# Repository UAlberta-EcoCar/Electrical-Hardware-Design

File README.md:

View this project on [CADLAB.io](https://cadlab.io/project/29517). 

# Electrical-Design-Hardware

**Do not merge branches to main yet, this may be done in the future**

Contains the hardware design for the upcoming prototype vehicle.  Each Branch in this repo has its own board design and schematic files for each car.  Add the entire repo to a filepath ia GitHub Desktop by adding the link into the "Current Repository" panel or with the following via a console:

```
cd Documents\GitHub                                                            #Change your directory where desired
git clone https://github.com/UAlberta-EcoCar/Electrical-Hardware-Design        #Clone the repo
cd Documents\GitHub\Electrical-Hardware-Design                                 #Change your directory into the repo
git branch -r                                                                  #Displays all remote branches, choose the branch you're looking for 
git checkout Relay-Board                                                       #branch that is desired (I used Relay-Board as an example).  
```
After making changes the remote branch can be updated with the following:
```
git add .                                                                      #Adds your modified files to the quene to be committed later
git commit -m "your-commit-message"                                            #Commits the files to a new revision of the branch with a log
git push                                                                       #Pushes the changes to the remote repo

#The following will pull the newest version of the remote repo:
git pull
```

If you want to see your local branches that you pulled or if you want to switch local branches do the following:

```
git branch                                                                     #Shows local branches (add -r for remote branches)
git switch <name-of-branch>                                                    #Switches branch

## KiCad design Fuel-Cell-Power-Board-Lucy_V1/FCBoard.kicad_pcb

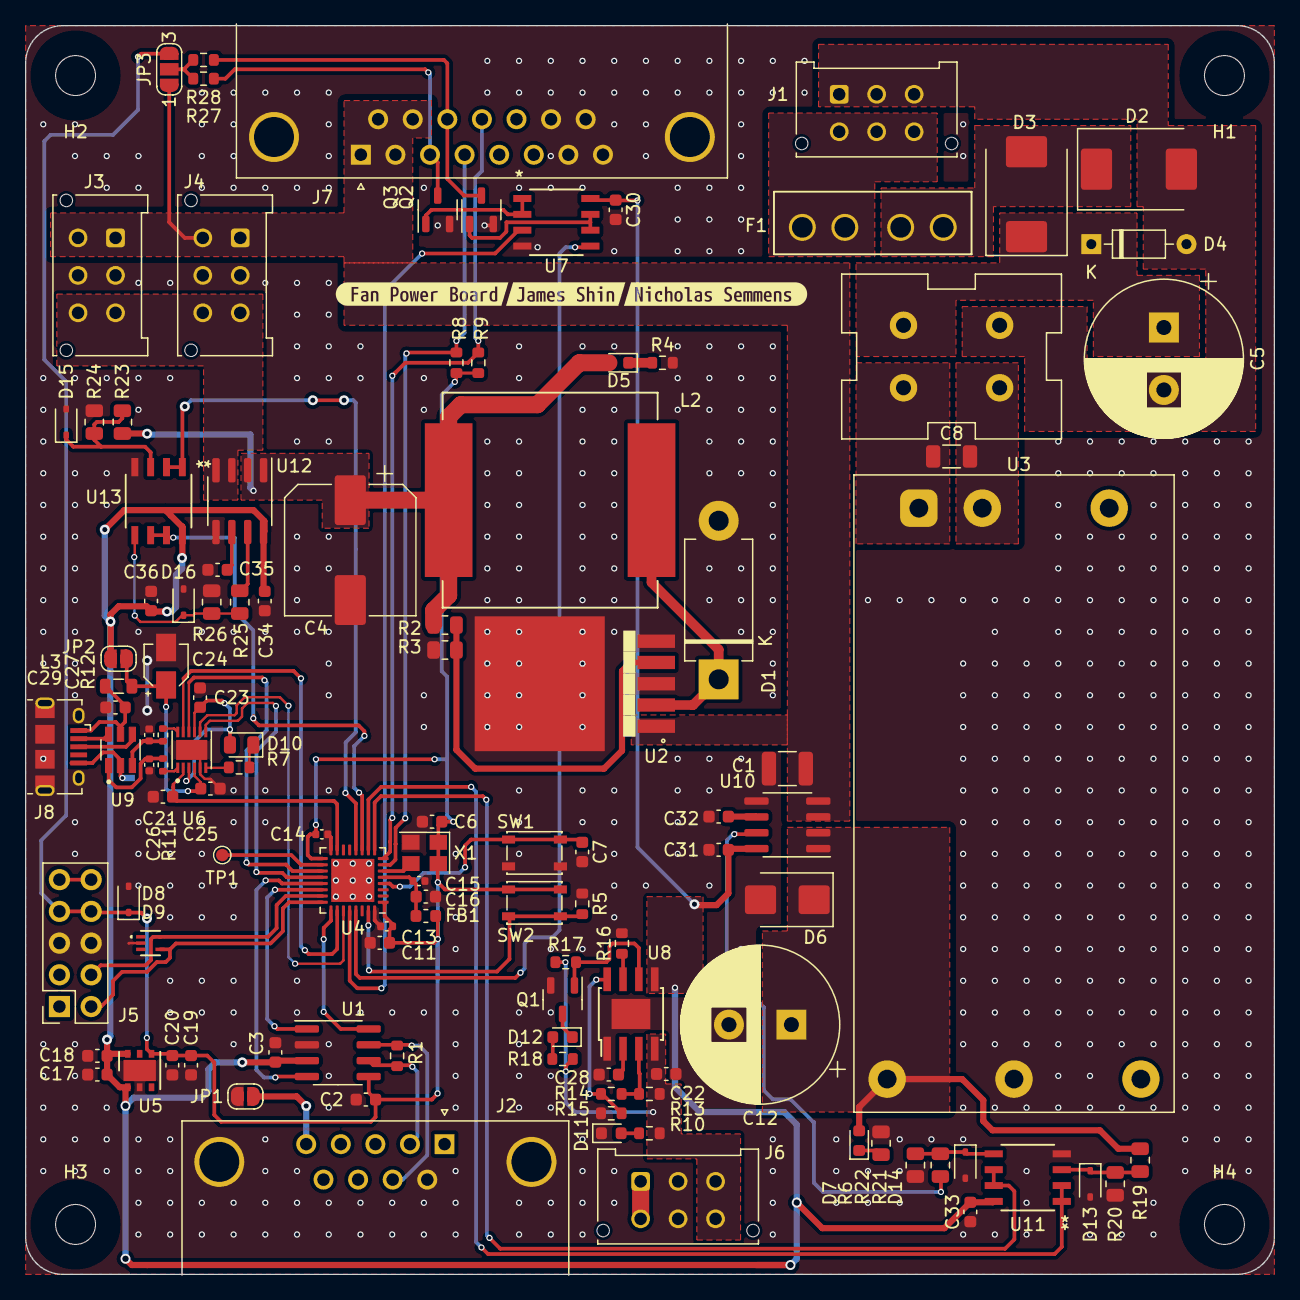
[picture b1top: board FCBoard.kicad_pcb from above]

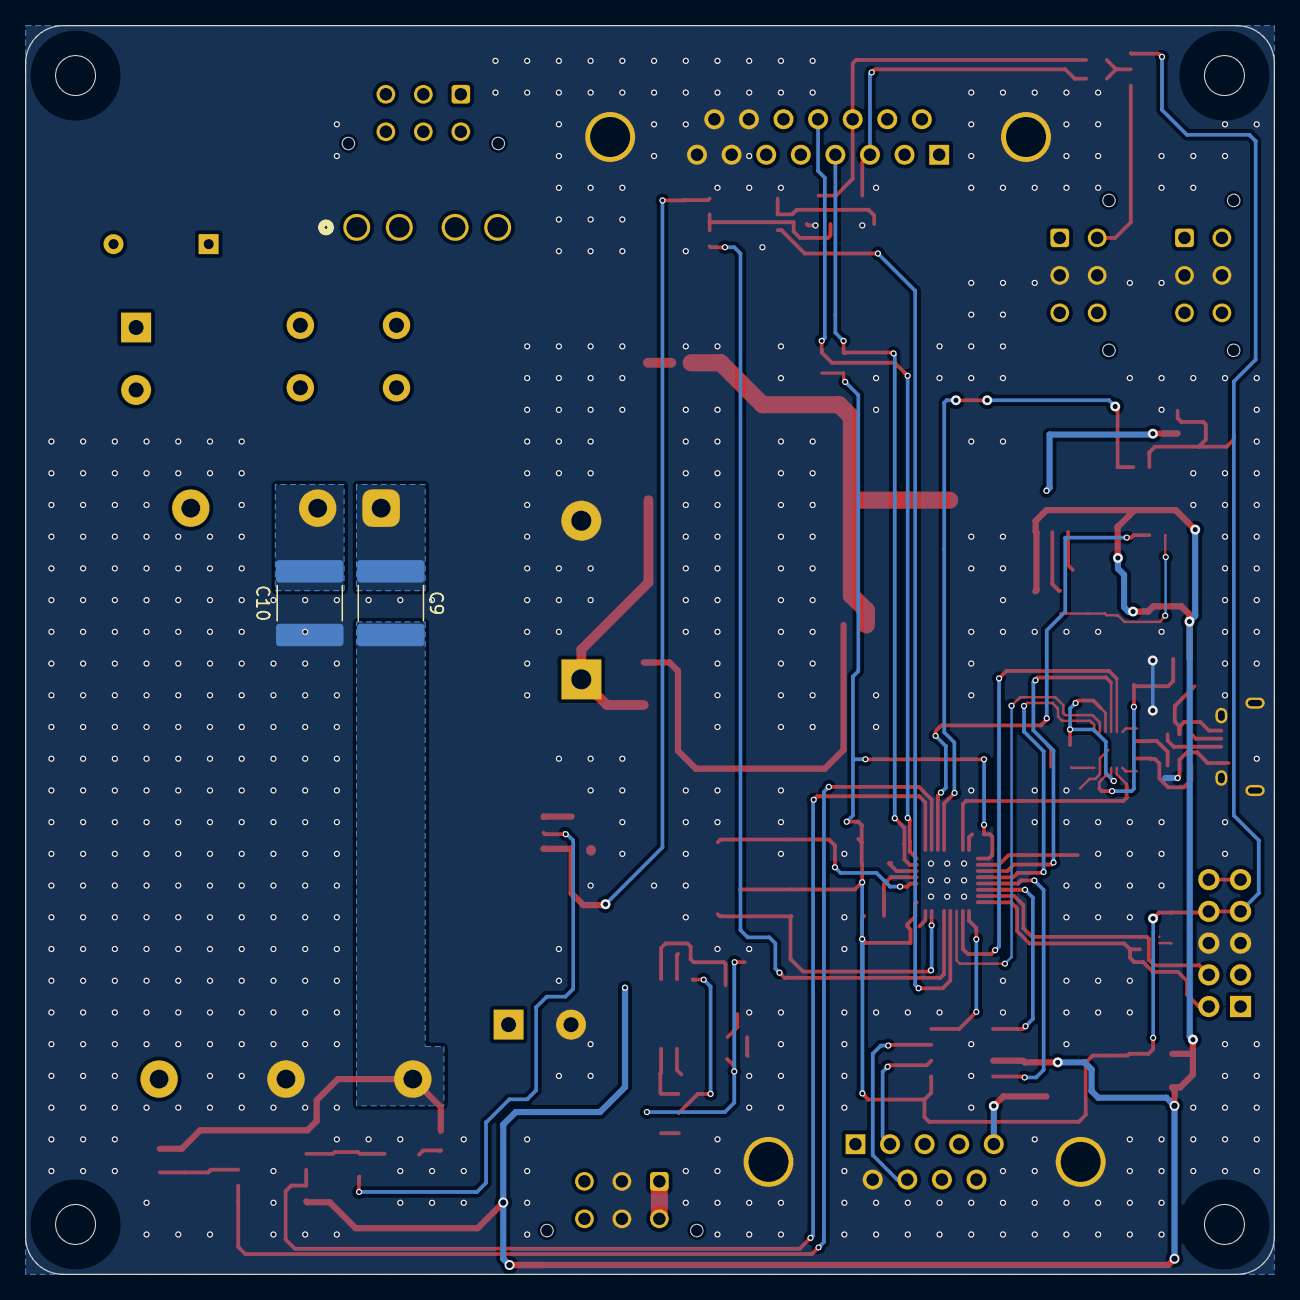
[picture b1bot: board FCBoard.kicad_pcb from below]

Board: 2 copper layers, 100.0 x 100.0 mm, 124 parts (3 on the bottom side), 79 nets.

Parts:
C1: 100u; C_1210_3225Metric
C2, C3, C6, C7, C18, C20, C21, C22, C23, C25, C29, C30: 100n; C_0603_1608Metric
C4: 1000u; CP_Elec_10x10
C5, C12: 100u; CP_Radial_D12.5mm_P5.00mm
C8: 10u; C_1206_3216Metric
C9, C10: 6.8n; C_2220_5650Metric
C11: 4u7; C_0603_1608Metric
C13, C14, C15: 100n; C_0402_1005Metric
C16, C17, C19: 1u; C_0603_1608Metric
C24: 4u7; CP_Elec_3x5.3
C26, C27: 47p; C_0402_1005Metric
C28: 2n2; C_0603_1608Metric
C31, C33, C34, C36: 0.1u; C_0603_1608Metric
C32, C35: 1n; C_0603_1608Metric
D1: 1N5822; D_DO-201AD_P12.70mm_Horizontal
D2: S10ML-TP; D_SMC
D3: SL44-E3_57T; D_SMC
D4: 1N5255B-TR; D_DO-35_SOD27_P7.62mm_Horizontal
D5, D7: LED; LED_0603_1608Metric
D6: SMBJ12A; D_SMB
D8, D13, D14, D15, D16: MM3Z3V3ST1GOSDKR-ND; D_SOD-323
D9: ESDALC6V1P5
D10: PINK; LED_0805_2012Metric
D11: BLUE; LED_0603_1608Metric
D12: RED; LED_0603_1608Metric
F1: CONN_3544-2_KEY
FB1: 300R; L_0603_1608Metric
FL1: Filter_EMI_LL_1423; CMC
H1, H2, H3, H4: MountingHole; MountingHole_3.2mm_M3
J1, J3, J4, J6: STD_PWR_HEADER
J2: DE9_Receptacle; DSUB-9_Female_Horizontal_P2.77x2.84mm_EdgePinOffset7.70mm_H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
J5: Conn_02x05_Odd_Even; PinSocket_2x05_P2.54mm_Vertical
J7: DA15_Receptacle_MountingHoles; DSUB-15_Female_Horizontal_P2.77x2.84mm_EdgePinOffset7.70mm_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
J8: USB_B_Micro; USB_Micro-B_Amphenol_10118194_Horizontal
JP1, JP2: SolderJumper_2_Open; SolderJumper-2_P1.3mm_Open_RoundedPad1.0x1.5mm
JP3: SolderJumper_3_Open; SolderJumper-3_P1.3mm_Open_RoundedPad1.0x1.5mm_NumberLabels
L2: 100u; L_Vishay_IHLP-6767
L3: 600R/0.5A; L_0805_2012Metric
NT1: NetTie_2; NetTie-2_SMD_Pad0.5mm
Q1, Q2, Q3: SI2302A-TPMSCT-ND; SOT-23-3
R1: 120; R_0603_1608Metric
R2: 0R; R_0805_2012Metric
R3, R20, R22, R24, R26: 1k; R_0805_2012Metric
R4: 560; R_0603_1608Metric
R5, R8, R9, R17, R27, R28: 10k; R_0603_1608Metric
R6, R23: 2k; R_0805_2012Metric
R7: 30.1; R_0603_1608Metric
R10: 150R; R_0603_1608Metric
R11, R12: 26.7; R_0402_1005Metric
R13: 150k; R_0603_1608Metric
R14: 7k87; R_0603_1608Metric
R15: 47k; R_0603_1608Metric
R16: 1k1; R_0603_1608Metric
R18: 120R; R_0603_1608Metric
R19: 2.7k; R_0805_2012Metric
R21, R25: 1.5k; R_0805_2012Metric
SW1, SW2: PTS815 SJM 250 SMTR LFS; SW_SPST_PTS810
TP1: MCO; TestPoint_Pad_D1.0mm
U1: MCP2542FD-E/SN; SOIC-8_3.9x4.9mm_P1.27mm
U2: LM2576D2TR4-5G; D2PAK-5
U3: RPA60-2412SFW; Converter_DCDC_RECOM_RPA60-xxxxSFW
U4: STM32L432KCUx; QFN-32-1EP_5x5mm_P0.5mm_EP3.45x3.45mm
U5: LD39050PU33R; DFN-6-1EP_3x3mm_P0.95mm_EP1.7x2.6mm
U6: FT234XD-R; SON45P300X300X80-13N
U7, U11, U13: TSV912IDT; SO8_STM
U8: TPS2596; TI_SO-PowerPAD-8
U9: USBLC6-2SC6
U10, U12: ACS712xLCTR-05B; SOIC-8_3.9x4.9mm_P1.27mm
X1: OXETDLJANF-8MHZ; Crystal_SMD_3225-4Pin_3.2x2.5mm
kibuzzard-65D3CBE6: G***; kibuzzard-65D3CBE6
kibuzzard-65D3CBF4: G***; kibuzzard-65D3CBF4
kibuzzard-65D3CC02: G***; kibuzzard-65D3CC02

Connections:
+5V: C3.2, C17.2, C18.2, C30.1, C31.2, C33.2, C34.2, C36.1, JP2.2 (B), U1.3 (VDD), U5.1 (EN), U5.6 (VI), U7.8 (V+), U8.5 (OUT), U10.8 (VCC), U11.8 (V+), U12.8 (VCC), U13.8 (V+)
/5V_Current_Meas1: U4.11 (PA5), U13.6 (-), U13.7
/5V_UP: C22.1, J6.3 (5V), J6.6 (5V), R10.1, R13.2, R17.1, R18.1, U8.4 (IN)
/5V_Voltage_Meas1: U4.12 (PA6), U13.1, U13.2 (-)
/12V_Current_Meas: U4.9 (PA3), U11.6 (-), U11.7
/12V_Voltage_Meas: U4.10 (PA4), U11.1, U11.2 (-)
/12V_{FC}: C1.1, J3.1 (12V), J3.4 (12V), J4.1 (12V), J4.4 (12V), J7.1, J7.2, J7.9, J7.10, JP3.1 (A), U2.1 (VIN), U10.3 (IP-), U10.4 (IP-)
/12V_{UP}: J6.1 (12V), J6.4 (12V)
/BOOT0: R5.2, SW2.1, U4.31 (PH3)
/CAN_H: J2.7, R1.2, U1.7 (CANH)
/CAN_L: J2.2, R1.1, U1.6 (CANL)
/CAN_{RXD}: U1.4 (RXD), U4.21 (PA11)
/CAN_{STBY}: U1.8 (STBY), U4.25 (PA15)
/CAN_{TXD}: U1.1 (TXD), U4.22 (PA12)
/D+: J8.3 (D+), U9.4
/D-: J8.2 (D-), U9.6
/DM: C26.1, R11.2, U9.1
/DP: C27.1, R12.2, U9.3
/FC+: F1.3, F1.4, J1.4 (12V), J1.5 (GND), J1.6 (5V)
/FC_5V_B1: J3.3 (5V), J3.6 (5V), J4.3 (5V), J4.6 (5V), U12.3 (IP-), U12.4 (IP-)
/FTDI_{~RST}: C21.2, U4.15 (PB1), U6.2 (~RESET#)
/GND_{1}: J8.5 (GND), NT1.2, U9.2
/I_{MON}5V: R16.1, U8.7 (ILM)
/MCU_3V3: C2.1, C6.1, C11.1, C13.1, C14.1, C19.2, C20.2, D8.1 (K), FB1.1, J5.7, J5.8, JP3.3 (B), R8.1, R9.1, SW2.2, U1.5 (VIO), U4.1 (VDD), U4.17 (VDD), U5.4 (VO), X1.1 (Tri-State), X1.4 (VDD)
/PA0: U4.6 (PA0), X1.3 (OUT)
/PA1: J7.4, R8.2, U4.7 (PA1)
/PA2: J7.12, R9.2, U4.8 (PA2)
/PA8: TP1.1, U4.18 (PA8)
/PA9: U4.19 (PA9), U6.10 (RXD)
/PA10: U4.20 (PA10), U6.7 (TXD)
/PA13: D9.5, J5.4, U4.23 (PA13)
/PA14: D9.4, J5.2, U4.24 (PA14)
/PB3: U4.26 (PB3), U6.11 (CTS#)
/PB4: U4.27 (PB4), U6.8 (RTS#)
/PB5: U4.28 (PB5), U7.3 (+)
/PB6: U4.29 (PB6), U7.5 (+)
/PWM_{1,Buff}: J7.3, Q3.3 (D), R27.1
/PWM_{2,Buff}: J7.11 (P111), Q2.3 (D), R28.1
/SHIELD: J2.5, JP1.2 (B)
/U_5V: J5.9, J5.10
/VCCIO: C23.1, D10.2 (A), U6.3 (3V3OUT), U6.9 (VCCIO)
/V_{BUS}: C29.1, J8.1 (VBUS), L3.2, U9.5
/VoltageCurrentSensing5V_1/Current_Sense_IN: C4.1, D5.2 (A), L2.2, R2.1, R23.1, U12.1 (IP+), U12.2 (IP+)
/VoltageCurrentSensing12V/Current_Sense_IN: C9.2, C12.1, D6.1 (K), D7.2 (A), R19.1, U3.6 (+VOUT), U10.1 (IP+), U10.2 (IP+)
/~FAULT: Q1.1 (G), R17.2, U8.6 (~FAULT)
/~RST: C7.1, SW1.2, U4.4 (NRST)
GND: C1.2, C2.2, C3.1, C4.2, C6.2, C7.2, C10.2, C11.2, C12.2, C13.2, C14.2, C15.2, C16.2, C17.1, C18.1, C19.1, C20.1, C21.1, C22.2, C23.2, C24.2, C25.2, C26.2, C27.2, C28.2, C29.2, C30.2, C31.1, C32.1, C33.1, C34.1, C35.1, C36.2, D1.2 (A), D6.2 (A), D8.2 (A), D9.2, D11.1 (K), D13.2 (A), D14.2 (A), D15.2 (A), D16.2 (A), J2.0 (PAD), J2.6, J3.2 (GND), J3.5 (GND), J4.2 (GND), J4.5 (GND), J5.5, J5.6, J6.2 (GND), J6.5 (GND), J7.0 (PAD), J7.7, J7.8, J7.14, J7.15, J8.6 (Shield), JP1.1 (A), NT1.1, Q1.2 (S), Q2.2 (S), Q3.2 (S), R3.2, R4.2, R5.1, R6.2, R15.2, R16.2, R20.1, R22.1, R24.1, R26.1, SW1.1, U1.2 (VSS), U2.3 (GND), U2.5 (ON/OFF), U2.6, U3.5 (-VOUT), U4.16 (VSS), U4.32 (VSS), U4.33 (VSS), U5.2 (GND), U5.7 (GND), U6.5 (GND), U6.13 (GND__1), U7.4 (V-), U8.1 (GND), U8.9 (PAD), U10.5 (GND), U11.4 (V-), U12.5 (GND), U13.4 (V-), X1.2 (GND)
GND1: C5.2, D2.2 (A), D4.2 (A), FL1.1, J1.1 (12V), J1.2 (GND), J1.3 (5V)
unnamed: D1.1 (K), L2.1, U2.2 (OUT)
unnamed: D2.1 (K), D3.2 (A), F1.1, F1.2
unnamed: C5.1, D3.1 (K), D4.1 (K), FL1.2
unnamed: D5.1 (K), R4.1
unnamed: D7.1 (K), R6.1
unnamed: D10.1 (K), R7.1
unnamed: D11.2 (A), R10.2
unnamed: D12.2 (A), R18.2
unnamed: D12.1 (K), Q1.3 (D)
unnamed: D13.1 (K), R19.2, R20.2, U11.3 (+)
unnamed: D14.1 (K), R21.2, R22.2, U11.5 (+)
unnamed: D15.1 (K), R23.2, R24.2, U13.3 (+)
unnamed: D16.1 (K), R25.2, R26.2, U13.5 (+)
unnamed: C24.1, C25.1, JP2.1 (A), L3.1, U6.4 (VCC)
unnamed: JP3.2 (C), R27.2, R28.2
unnamed: Q2.1 (G), U7.6 (-), U7.7
unnamed: Q3.1 (G), U7.1, U7.2 (-)
unnamed: R2.2, R3.1, U2.4 (FB)
unnamed: C8.1, C9.1, FL1.3, U3.1 (+VIN)
unnamed: C8.2, C10.1, FL1.4, U3.2 (-VIN)
unnamed: C15.1, C16.1, FB1.2, U4.5 (VDDA)
unnamed: R7.2, U6.6 (CBUS0)
unnamed: R11.1, U6.1 (USBDM)
unnamed: R12.1, U6.12 (USBDP)
unnamed: R13.1, R14.1, U8.3 (EN/UVLO)
unnamed: R14.2, R15.1, U8.8 (OVLO)
unnamed: C28.1, U8.2 (dV/dT)
unnamed: C32.2, U10.6 (FILTER)
unnamed: R21.1, U10.7 (VIOUT)
unnamed: C35.2, U12.6 (FILTER)
unnamed: R25.1, U12.7 (VIOUT)

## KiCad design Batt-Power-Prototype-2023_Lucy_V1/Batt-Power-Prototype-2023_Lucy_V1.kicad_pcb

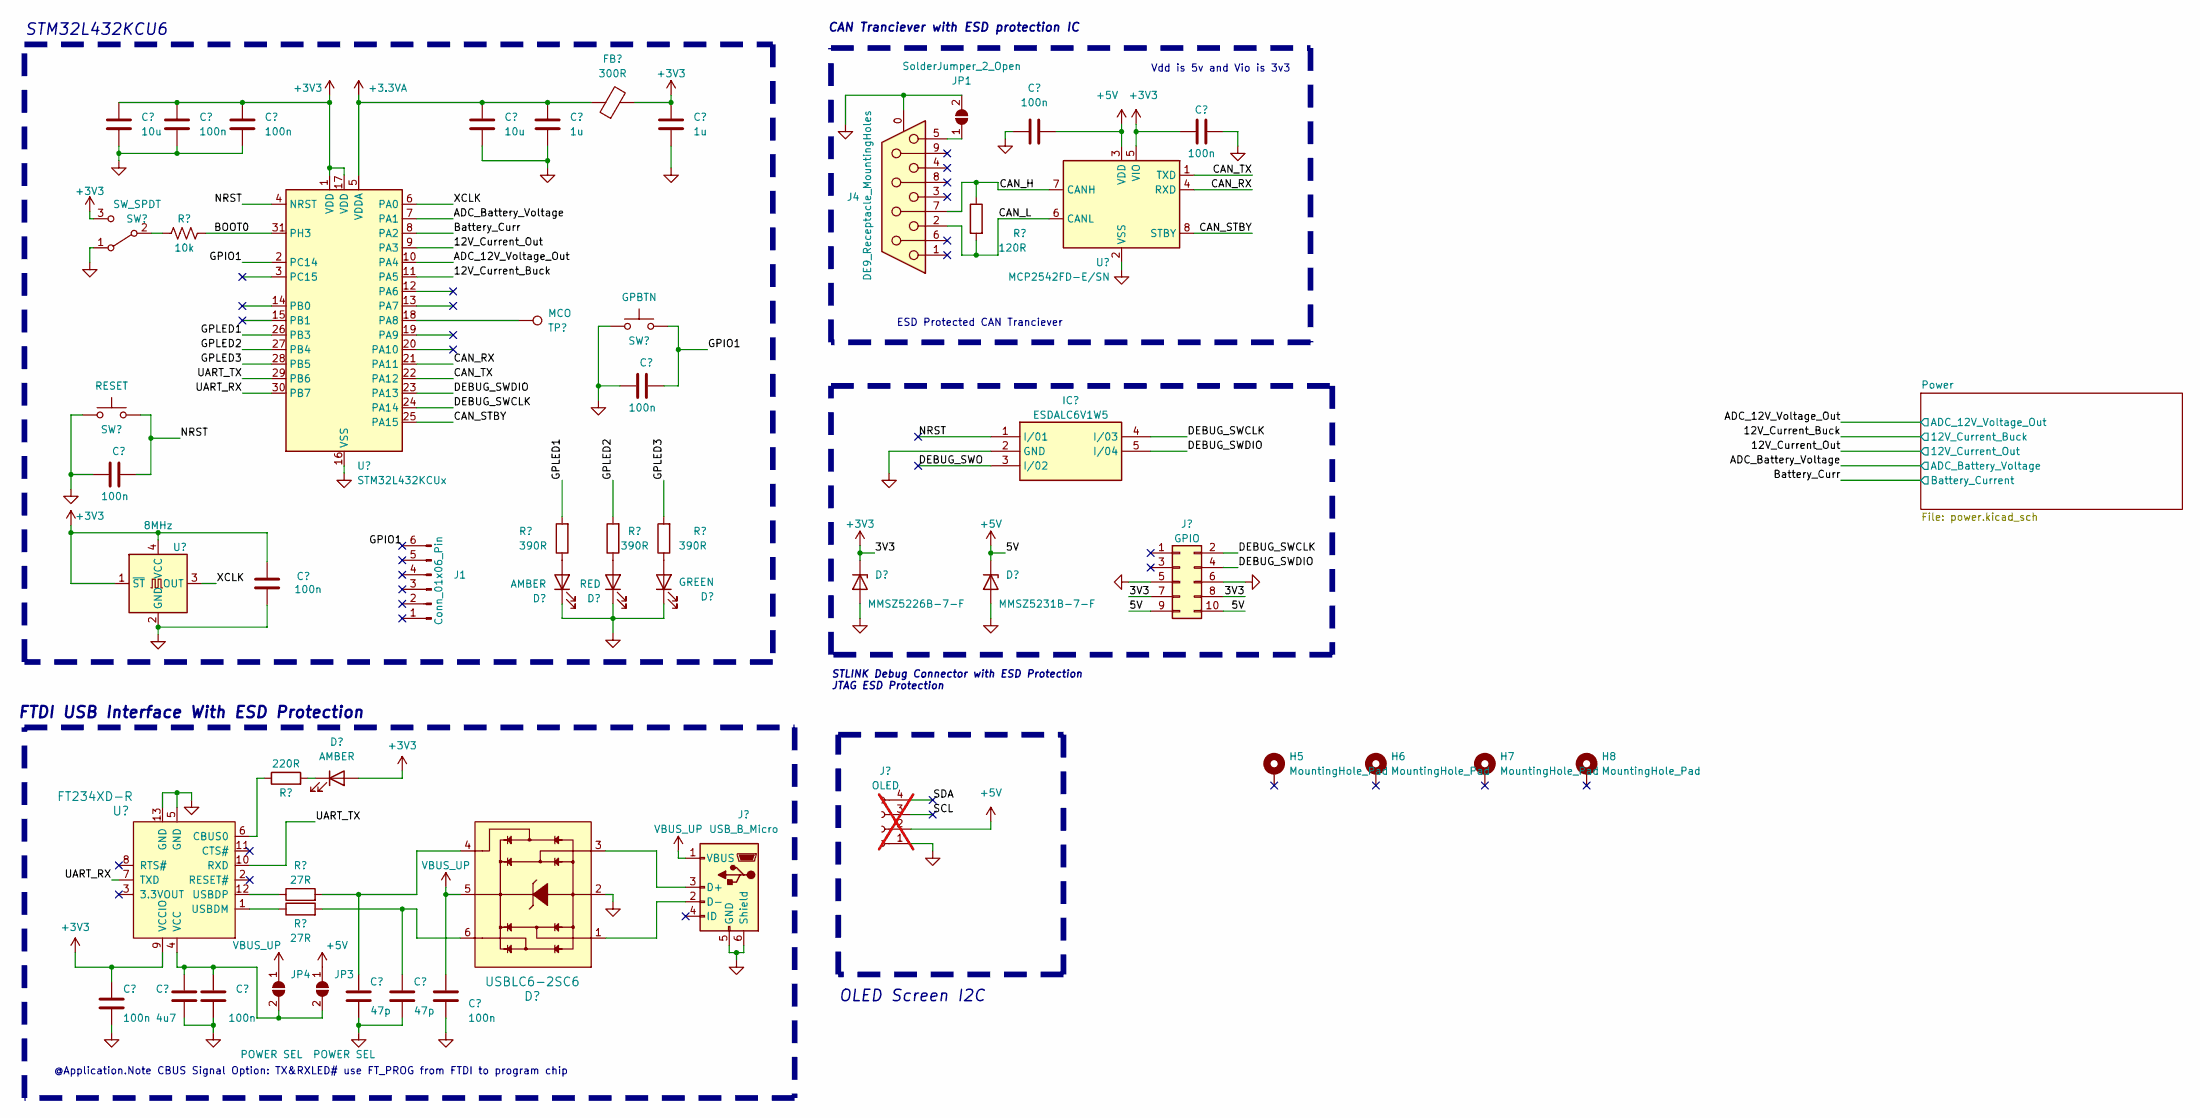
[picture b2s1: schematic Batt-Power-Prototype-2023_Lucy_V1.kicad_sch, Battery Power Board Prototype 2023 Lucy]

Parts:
C1, C2, C4, C6, C7, C8, C11, C15, C16, C55: 100n; C_0402_1005Metric; JLCPCB Part#(Optional) C1525
C3, C12: 10u; C_0603_1608Metric; JLCPCB Part#(Optional) C96446
C5: 4u7; C_0603_1608Metric; JLCPCB Part#(Optional) C1779
C9, C10: 47p; C_0402_1005Metric; JLCPCB Part#(Optional) C1671
C13, C14: 1u; C_0603_1608Metric; JLCPCB Part#(Optional) C28323
D1, D3: AMBER; LED_0805_2012Metric; JLCPCB Part#(Optional) C2296
D2: USBLC6-2SC6; SOT23-6L_STM-L; Digikey # 497-5235-1-ND
D4: RED; LED_0805_2012Metric; JLCPCB Part#(Optional) C84256
D5: GREEN; LED_0805_2012Metric; JLCPCB Part#(Optional) C2297
D6: MMSZ5226B-7-F; D_SOD-123; Digikey # MMSZ5226B-FDICT-ND
D7: MMSZ5231B-7-F; D_SOD-123; Digikey # MMSZ5231B-7-F
FB1: 300R; L_0603_1608Metric; Digikey # 1934-1474-1-ND
H5, H6, H7, H8: MountingHole_Pad; MountingHole_3.2mm_M3_Pad
IC1: ESDALC6V1W5; SOT65P210X110-5N; JLCPCB Part#(Optional) C2827626
J1: Conn_01x06_Pin; PinHeader_2x03_P2.54mm_Vertical
J2: USB_B_Micro; USB_Micro-B_Amphenol_10118194_Horizontal; Digikey # 609-4618-1-ND
J3: OLED; Display_128x64_096_I2C; not fitted
J4: DE9_Receptacle_MountingHoles; DSUB-9_Female_Horizontal_P2.77x2.84mm_EdgePinOffset7.70mm_H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
J5: GPIO; PinHeader_2x05_P2.54mm_Vertical; JLCPCB Part#(Optional) C5116482
JP1: SolderJumper_2_Open; SolderJumper-2_P1.3mm_Open_RoundedPad1.0x1.5mm
JP3, JP4: POWER SEL; SolderJumper-2_P1.3mm_Open_TrianglePad1.0x1.5mm
R1: 10k; R_0805_2012Metric; JLCPCB Part#(Optional) C17414
R2: 220R; R_0805_2012Metric; JLCPCB Part#(Optional) C17557
R3, R4: 27R; R_0402_1005Metric; JLCPCB Part#(Optional) C25190
R5, R6, R7: 390R; R_0805_2012Metric; JLCPCB Part#(Optional) C17655
R8: 120R; R_0603_1608Metric
SW1: RESET; SW_PUSH_6mm_H5mm
SW2: SW_SPDT; SW_SPDT_PCM12; Digikey # 2223-SLW-66527511-SMT-TRCT-ND
SW3: GPBTN; SW_PUSH_6mm_H5mm
TP1: MCO; TestPoint_Pad_D1.0mm
U1: 8MHz; Crystal_SMD_3225-4Pin_3.2x2.5mm; Digikey # 535-ASE-8.000MHZ-L-C-TCT-ND
U2: FT234XD-R; JLCPCB Part#(Optional) C132158
U3: STM32L432KCUx; QFN-32-1EP_5x5mm_P0.5mm_EP3.45x3.45mm; JLCPCB Part#(Optional) C1337280
U4: MCP2542FD-E/SN; SOIC-8_3.9x4.9mm_P1.27mm; Digikey # MCP2542FD-E/SN-ND

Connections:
+3.3VA: C12.1, C13.1, FB1.1, U3.5 (VDDA)
+3V3: C1.1, C3.1, C4.1, C6.1, C8.2, C14.1, C16.2, D1.2 (A), D6.1 (K), FB1.2, J5.7, J5.8, SW2.3 (C), U1.1 (~ST), U1.4 (VCC), U2.9 (VCCIO), U3.1 (VDD), U3.17 (VDD), U4.5 (VIO); also elsewhere on the board
+5V: C15.2, D7.1 (K), J3.2, J5.9, J5.10, JP3.1 (A), U4.3 (VDD); also elsewhere on the board
/12V_Current_Buck: U3.11 (PA5); also elsewhere on the board
/12V_Current_Out: U3.9 (PA3); also elsewhere on the board
/ADC_12V_Voltage_Out: U3.10 (PA4); also elsewhere on the board
/ADC_Battery_Voltage: U3.7 (PA1); also elsewhere on the board
/BOOT0: R1.2, U3.31 (PH3)
/Battery_Curr: U3.8 (PA2); also elsewhere on the board
/CAN_H: J4.7, R8.1, U4.7 (CANH)
/CAN_L: J4.2, R8.2, U4.6 (CANL)
/CAN_RX: U3.21 (PA11), U4.4 (RXD)
/CAN_STBY: U3.25 (PA15), U4.8 (STBY)
/CAN_TX: U3.22 (PA12), U4.1 (TXD)
/DEBUG_SWCLK: IC1.4 (I/03), J5.2, U3.24 (PA14)
/DEBUG_SWDIO: IC1.5 (I/04), J5.4, U3.23 (PA13)
/DEBUG_SWO: IC1.3 (I/02)
/GPIO1: C55.2, J1.6, SW3.2, U3.2 (PC14)
/GPLED1: R5.2, U3.26 (PB3)
/GPLED2: R6.2, U3.27 (PB4)
/GPLED3: R7.2, U3.28 (PB5)
/NRST: C2.2, IC1.1 (I/01), SW1.2, U3.4 (NRST)
/UART_RX: U2.7 (TXD), U3.30 (PB7)
/UART_TX: U2.10 (RXD), U3.29 (PB6)
/XCLK: U1.3 (OUT), U3.6 (PA0)
GND: C1.2, C2.1, C3.2, C4.2, C5.2, C6.2, C7.2, C8.1, C9.1, C10.1, C11.1, C12.2, C13.2, C14.2, C15.1, C16.1, C55.1, D2.2, D3.1 (K), D4.1 (K), D5.1 (K), D6.2 (A), D7.2 (A), IC1.2 (GND), J2.5 (GND), J2.6 (Shield), J3.1, J4.0 (PAD), J5.5, J5.6, JP1.2 (B), SW1.1, SW2.1 (A), SW3.1, U1.2 (GND), U2.5 (GND), U2.13 (GND), U3.16 (VSS), U3.32 (VSS), U3.33 (VSS), U4.2 (VSS), U4.9 (VSS); also elsewhere on the board
unnamed: C9.2, D2.4, R3.2
unnamed: C10.2, D2.6, R4.2
unnamed: D1.1 (K), R2.2
unnamed: D3.2 (A), R5.1
unnamed: D4.2 (A), R6.1
unnamed: D5.2 (A), R7.1
unnamed: D2.3, J2.3 (D+)
unnamed: D2.1, J2.2 (D-)
unnamed: J4.5, JP1.1 (A)
unnamed: C5.1, C7.1, JP3.2 (B), JP4.2 (B), U2.4 (VCC)
unnamed: R1.1, SW2.2 (B)
unnamed: R2.1, U2.6 (CBUS0)
unnamed: R4.1, U2.1 (USBDM)
unnamed: R3.1, U2.12 (USBDP)
unnamed: TP1.1, U3.18 (PA8)
VBUS_UP: C11.2, D2.5, J2.1 (VBUS), JP4.1 (A)

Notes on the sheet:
CAN Tranciever with ESD protection IC
STM32L432KCU6
@Application.Note CBUS Signal Option: TX&RXLED# use FT_PROG from FTDI to program chip
Vdd is 5v and Vio is 3v3
OLED Screen I2C
FTDI USB Interface With ESD Protection
STLINK Debug Connector with ESD Protection JTAG ESD Protection
ESD Protected CAN Tranciever

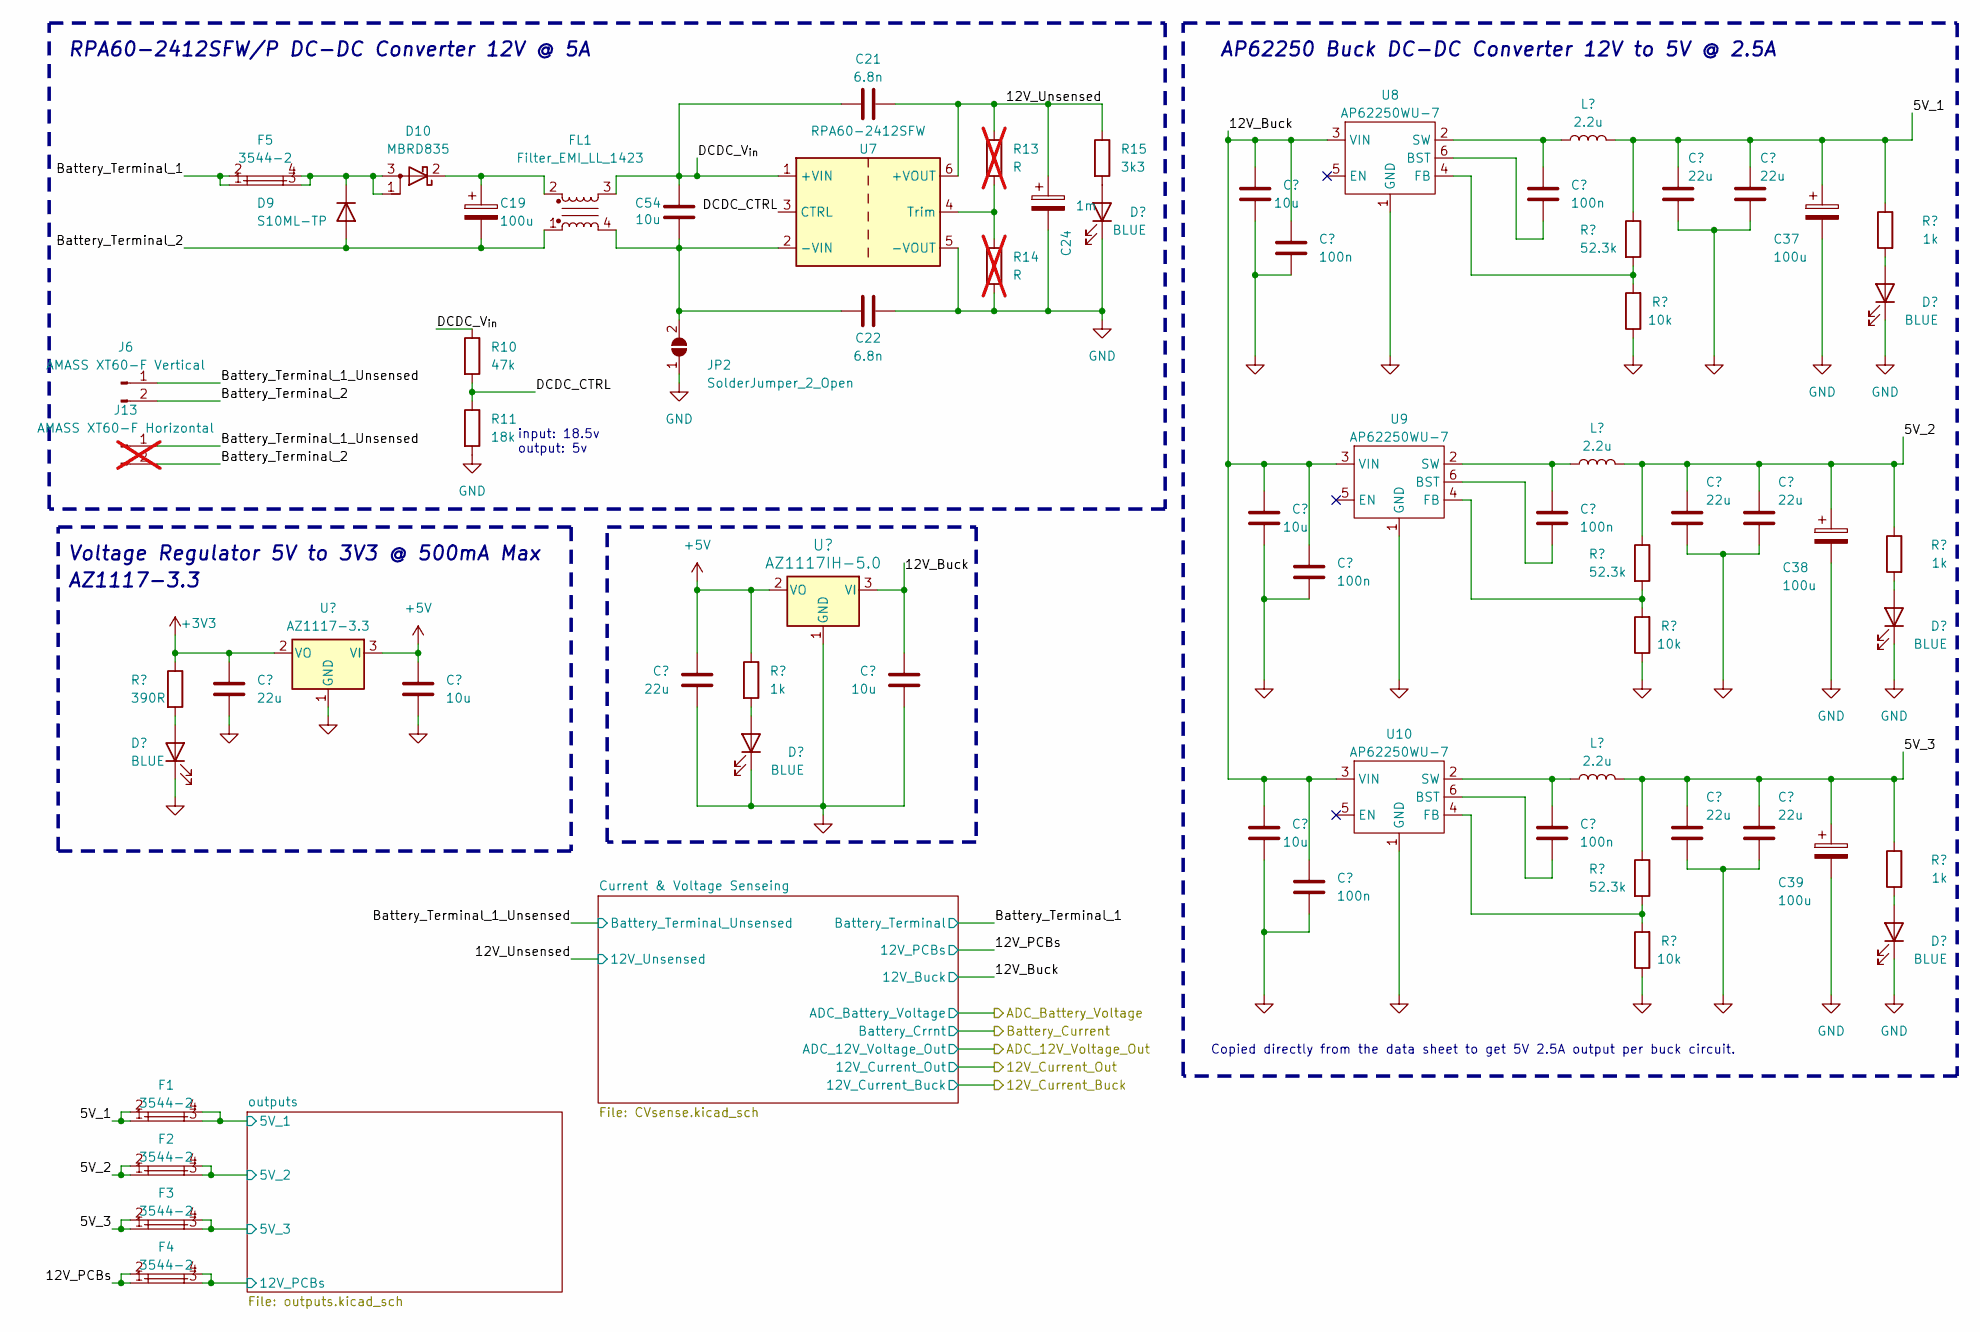
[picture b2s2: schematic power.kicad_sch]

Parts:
C17: 22u; C_0603_1608Metric; Digikey # 490-7612-2-ND
C18: 10u; C_0603_1608Metric; Digikey # 490-14381-1-ND
C19: 100u; CP_Radial_D10.0mm_P5.00mm; Digikey # 399-ESH107M100AH4AA-ND
C20: 22u; C_0603_1608Metric; JLCPCB Part#(Optional) C45783
C21, C22: 6.8n; CAP_2220_AVX; Digikey # 478-5929-2-ND
C23: 10u; C_0603_1608Metric; JLCPCB Part#(Optional) C96446
C24: 1m; CP_Radial_D12.5mm_P5.00mm; Digikey # 4191-PF1V102MP51020RCT-ND
C25, C26, C27: 10u; C_1210_3225Metric
C28, C29, C30, C51, C52, C53: 100n; C_0603_1608Metric; Digikey # CC0603KRX7R7BB104
C31, C32, C33, C34, C35, C36: 22u; C_1210_3225Metric
C37, C38, C39: 100u; CP_Elec_6.3x7.7; Digikey # P10387TB-ND
C54: 10u; CAPC3225X270N; Digikey # 445-4536-1-ND
D8, D11, D12, D13, D14, D15: BLUE; LED_0805_2012Metric; Digikey # 160-1647-1-ND
D9: S10ML-TP; D_SMC; Digikey # S10ML-TPMSCT-ND
D10: MBRD835; TO-252-2; Digikey # 1655-MBRD835CT-ND
F1, F2, F3, F4, F5: 3544-2; CONN_3544-2_KEY; Digikey # 36-3544-2-ND
FL1: Filter_EMI_LL_1423; CMC; Digikey # 732-3884-ND
J6: AMASS XT60-F Vertical; XT-60_female
J13: AMASS XT60-F Horizontal; AMASS_XT60PW-F; not fitted
JP2: SolderJumper_2_Open; SolderJumper-2_P1.3mm_Open_RoundedPad1.0x1.5mm
L1, L2, L3: 2.2u; L_7.3x7.3_H3.5; Digikey # 732-13496-1-ND
R9: 390R; R_0805_2012Metric; Digikey # RMCF0805JT390R
R10: 47k; R_1210_3225Metric; Digikey # RC1210FR-0747KL
R11: 18k; R_1210_3225Metric; Digikey # 2019-RK73B2ETTD183JCT-ND
R12, R22, R23, R24: 1k; R_0805_2012Metric; JLCPCB Part#(Optional) C28636
R13, R14: R; R_0805_2012Metric; not fitted
R15: 3k3; R_0805_2012Metric; JLCPCB Part#(Optional) C26010
R16, R18, R20: 52.3k; R_0603_1608Metric; Digikey # RMCF0603FT52K3CT-ND
R17, R19, R21: 10k; R_0603_1608Metric; JLCPCB Part#(Optional) C25804
U5: AZ1117-3.3; SOT-223-3_TabPin2; Digikey # AZ1117IH-3.3TRG1DICT-ND
U6: AZ1117IH-5.0; SOT-223-3_TabPin2; Digikey # AZ1117IH-5.0TRG1DICT-ND
U7: RPA60-2412SFW; Converter_DCDC_RECOM_RPA60-xxxxSFW; Digikey # 945-2958-ND
U8, U9, U10: AP62250WU-7; TSOT-23-6

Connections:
+3V3: C17.1, R9.1, U5.2 (VO); also elsewhere on the board
+5V: C18.1, C20.1, R12.1, U5.3 (VI), U6.2 (VO); also elsewhere on the board
/Power/5V_1: C31.1, C34.1, C37.1, F1.1, F1.2, L1.2, R16.1, R22.1
/Power/5V_2: C32.1, C35.1, C38.1, F2.1, F2.2, L2.2, R18.1, R23.1
/Power/5V_3: C33.1, C36.1, C39.1, F3.1, F3.2, L3.2, R20.1, R24.1
/Power/12V_Buck: C23.1, C25.1, C26.1, C27.1, C51.1, C52.1, C53.1, U6.3 (VI), U8.3 (VIN), U9.3 (VIN), U10.3 (VIN); also elsewhere on the board
/Power/12V_PCBs: F4.1, F4.2; also elsewhere on the board
/Power/12V_Unsensed: C21.2, C24.1, R13.1, R15.1, U7.6 (+VOUT); also elsewhere on the board
/Power/Battery_Terminal_1: F5.1, F5.2; also elsewhere on the board
/Power/Battery_Terminal_1_Unsensed: J6.1, J13.1; also elsewhere on the board
/Power/Battery_Terminal_2: C19.2, D9.2 (A), FL1.1, J6.2, J13.2
/Power/DCDC_CTRL: R10.2, R11.1, U7.3 (CTRL)
/Power/DCDC_V_{in}: C21.1, C54.1, FL1.3, R10.1, U7.1 (+VIN)
/Power/outputs/5V_1: F1.3, F1.4; also elsewhere on the board
/Power/outputs/5V_2: F2.3, F2.4; also elsewhere on the board
/Power/outputs/5V_3: F3.3, F3.4; also elsewhere on the board
/Power/outputs/12V_PCBs: F4.3, F4.4; also elsewhere on the board
GND: C17.2, C18.2, C20.2, C22.2, C23.2, C24.2, C25.2, C26.2, C27.2, C31.2, C32.2, C33.2, C34.2, C35.2, C36.2, C37.2, C38.2, C39.2, C51.2, C52.2, C53.2, D8.1 (K), D11.1 (K), D12.1 (K), D13.1 (K), D14.1 (K), D15.1 (K), JP2.1 (A), R11.2, R14.2, R17.1, R19.1, R21.1, U5.1 (GND), U6.1 (GND), U7.5 (-VOUT), U8.1 (GND), U9.1 (GND), U10.1 (GND); also elsewhere on the board
unnamed: D8.2 (A), R9.2
unnamed: D9.1 (K), D10.1 (A), D10.3 (A), F5.3, F5.4
unnamed: C19.1, D10.2 (K), FL1.2
unnamed: D11.2 (A), R12.2
unnamed: D12.2 (A), R15.2
unnamed: D13.2 (A), R22.2
unnamed: D14.2 (A), R23.2
unnamed: D15.2 (A), R24.2
unnamed: C22.1, C54.2, FL1.4, JP2.2 (B), U7.2 (-VIN)
unnamed: R13.2, R14.1, U7.4 (Trim)
unnamed: C28.2, U8.6 (BST)
unnamed: R16.2, R17.2, U8.4 (FB)
unnamed: C28.1, L1.1, U8.2 (SW)
unnamed: C29.2, U9.6 (BST)
unnamed: R18.2, R19.2, U9.4 (FB)
unnamed: C29.1, L2.1, U9.2 (SW)
unnamed: C30.2, U10.6 (BST)
unnamed: R20.2, R21.2, U10.4 (FB)
unnamed: C30.1, L3.1, U10.2 (SW)

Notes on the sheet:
AZ1117-3.3
Voltage Regulator 5V to 3V3 @ 500mA Max
RPA60-2412SFW/P DC-DC Converter 12V @ 5A
AP62250 Buck DC-DC Converter 12V to 5V @ 2.5A
Copied directly from the data sheet to get 5V 2.5A output per buck circuit.
input: 18.5v output: 5v

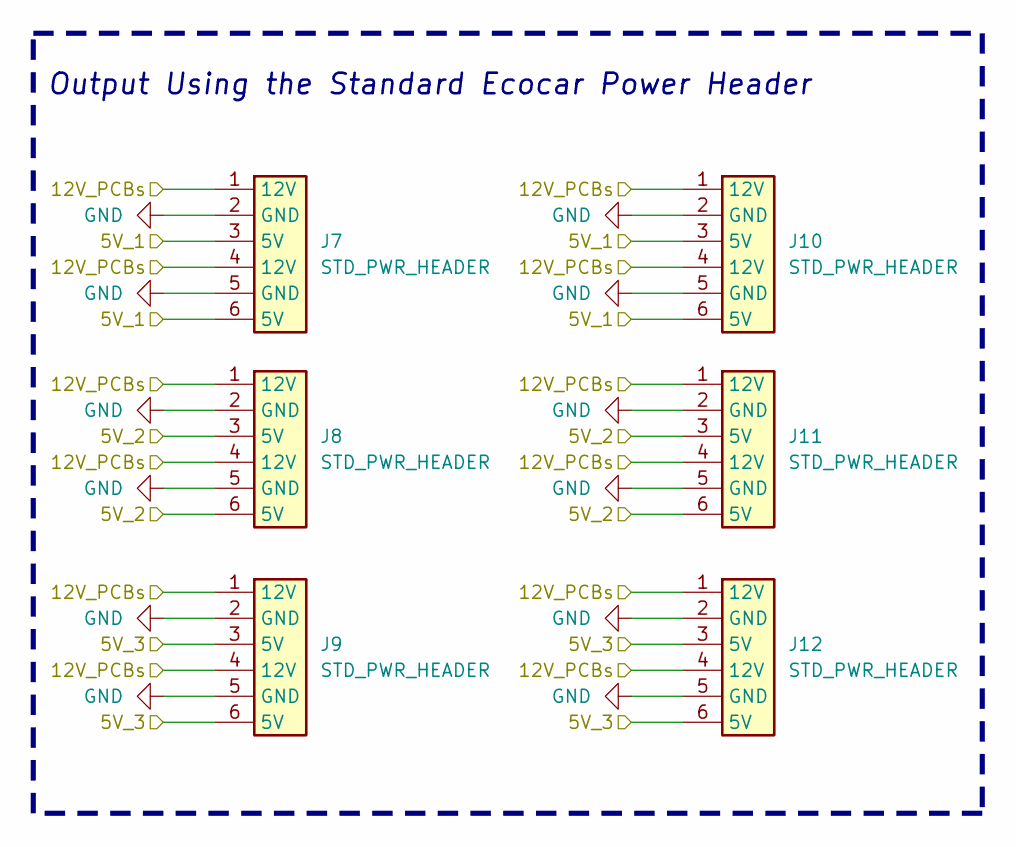
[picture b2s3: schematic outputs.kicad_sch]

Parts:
J7, J8, J9, J10, J11, J12: STD_PWR_HEADER; CON_430450612_MOL

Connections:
/Power/outputs/5V_1: J7.3 (5V), J7.6 (5V), J10.3 (5V), J10.6 (5V); also elsewhere on the board
/Power/outputs/5V_2: J8.3 (5V), J8.6 (5V), J11.3 (5V), J11.6 (5V); also elsewhere on the board
/Power/outputs/5V_3: J9.3 (5V), J9.6 (5V), J12.3 (5V), J12.6 (5V); also elsewhere on the board
/Power/outputs/12V_PCBs: J7.1 (12V), J7.4 (12V), J8.1 (12V), J8.4 (12V), J9.1 (12V), J9.4 (12V), J10.1 (12V), J10.4 (12V), J11.1 (12V), J11.4 (12V), J12.1 (12V), J12.4 (12V); also elsewhere on the board
GND: J7.2 (GND), J7.5 (GND), J8.2 (GND), J8.5 (GND), J9.2 (GND), J9.5 (GND), J10.2 (GND), J10.5 (GND), J11.2 (GND), J11.5 (GND), J12.2 (GND), J12.5 (GND); also elsewhere on the board

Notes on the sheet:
Output Using the Standard Ecocar Power Header
